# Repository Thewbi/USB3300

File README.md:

# USB3300
STM32F405RGT6 + USB3300

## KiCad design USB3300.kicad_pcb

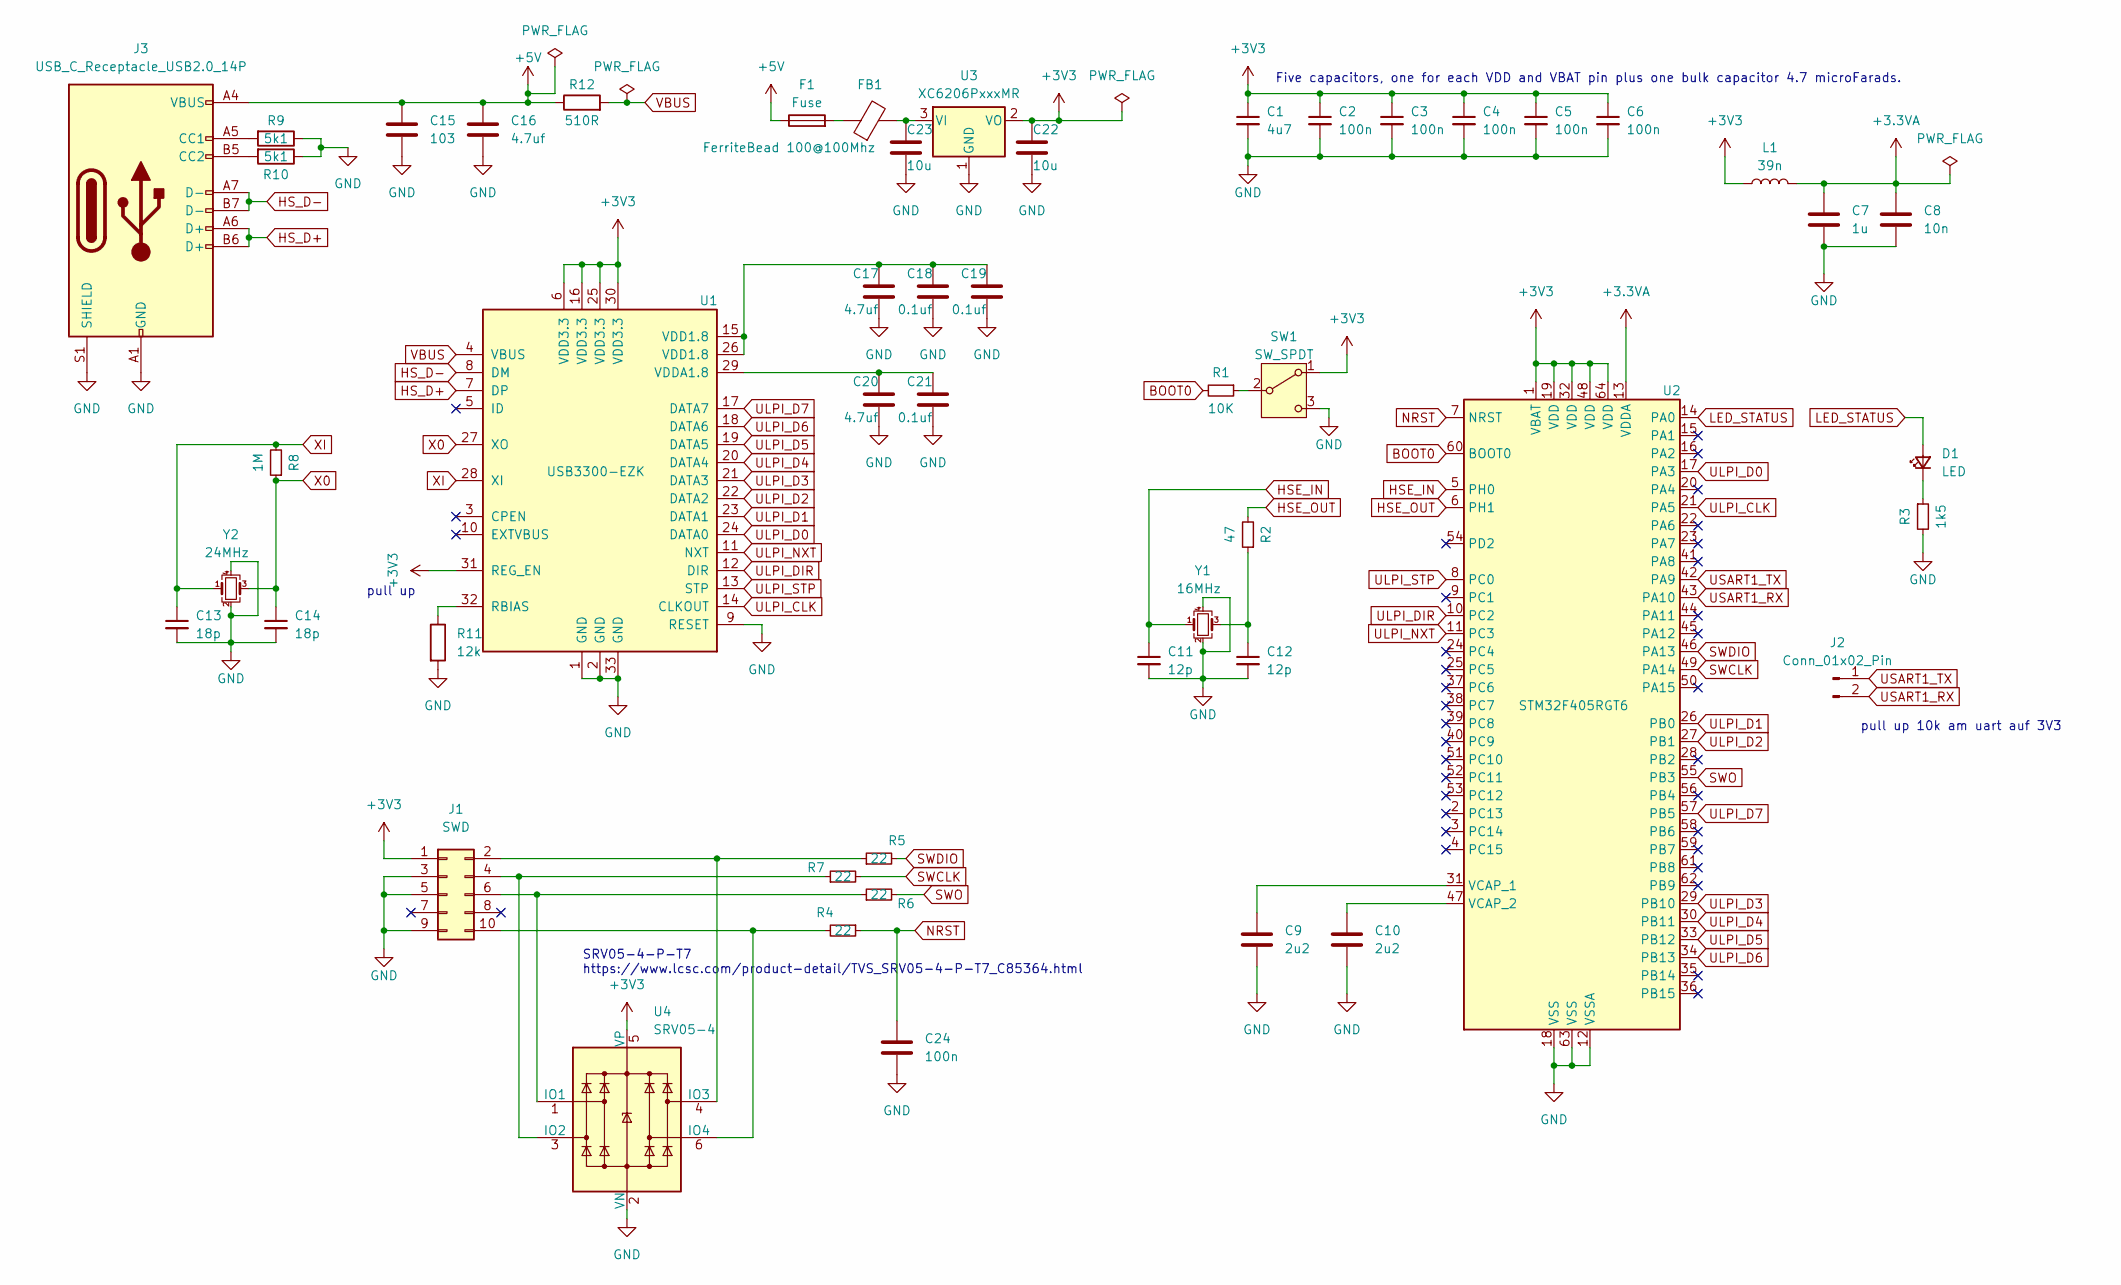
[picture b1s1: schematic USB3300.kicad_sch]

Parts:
C1: 4u7; C_0603_1608Metric
C2, C3, C4, C5, C6: 100n; C_0603_1608Metric
C7: 1u; C_0603_1608Metric
C8: 10n; C_0603_1608Metric
C9, C10: 2u2; C_0603_1608Metric
C11, C12: 12p; C_0402_1005Metric
C13, C14: 18p; C_0603_1608Metric
C15: 103; C_0603_1608Metric
C16, C17, C20: 4.7uf; C_0603_1608Metric
C18, C19, C21: 0.1uf; C_0603_1608Metric
C22, C23: 10u; C_0603_1608Metric
C24: 100n
D1: LED; LED_0402_1005Metric
F1: Fuse; Fuse_1206_3216Metric_Pad1.42x1.75mm_HandSolder
FB1: FerriteBead 100@100Mhz; LairdTech_28C0236-0JW-10
J1: SWD; PinHeader_2x05_P1.27mm_Vertical_SMD
J2: Conn_01x02_Pin; PinHeader_1x02_P2.54mm_Vertical
J3: USB_C_Receptacle_USB2.0_14P; USB_C_Receptacle_HRO_TYPE-C-31-M-12
L1: 39n; L_0603_1608Metric
R1: 10K; R_0603_1608Metric
R2: 47; R_0603_1608Metric
R3: 1k5; R_0603_1608Metric
R4, R5, R6, R7: 22; R_0603_1608Metric
R8: 1M; R_0603_1608Metric
R9, R10: 5k1; R_0603_1608Metric
R11: 12k; R_0603_1608Metric
R12: 510R; R_0603_1608Metric
SW1: SW_SPDT; SW_SPDT_PCM12
U1: USB3300-EZK; QFN-32-1EP_5x5mm_P0.5mm_EP3.45x3.45mm
U2: STM32F405RGT6; LQFP-64_10x10mm_P0.5mm
U3: XC6206PxxxMR; SOT-23-3
U4: SRV05-4; SOT-23-6
Y1: 16MHz; Crystal_SMD_3225-4Pin_3.2x2.5mm
Y2: 24MHz; Crystal_SMD_3225-4Pin_3.2x2.5mm

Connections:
+3.3VA: C7.1, C8.1, L1.2, U2.13 (VDDA)
+3V3: C1.1, C2.1, C3.1, C4.1, C5.1, C6.1, C22.1, J1.1, L1.1, SW1.1 (A), U1.6 (VDD3.3), U1.16 (VDD3.3), U1.25 (VDD3.3), U1.30 (VDD3.3), U1.31 (REG_EN), U2.1 (VBAT), U2.19 (VDD), U2.32 (VDD), U2.48 (VDD), U2.64 (VDD), U3.2 (VO), U4.5 (VP)
+5V: C15.1, C16.1, F1.1, J3.A4 (VBUS), J3.A9 (VBUS), J3.B4 (VBUS), J3.B9 (VBUS), R12.1
BOOT0: R1.2, U2.60 (BOOT0)
GND: C1.2, C2.2, C3.2, C4.2, C5.2, C6.2, C7.2, C8.2, C9.2, C10.2, C11.2, C12.2, C13.2, C14.2, C15.2, C16.2, C17.2, C18.2, C19.2, C20.2, C21.2, C22.2, C23.2, C24.2, J1.3, J1.5, J1.9, J3.A1 (GND), J3.A12 (GND), J3.B1 (GND), J3.B12 (GND), J3.S1 (SHIELD), R3.2, R9.1, R10.1, R11.2, SW1.3 (C), U1.1 (GND), U1.2 (GND), U1.9 (RESET), U1.33 (GND), U2.12 (VSSA), U2.18 (VSS), U2.63 (VSS), U3.1 (GND), U4.2 (VN), Y1.2, Y1.4, Y2.2, Y2.4
HSE_IN: C11.1, U2.5 (PH0), Y1.1
HSE_OUT: R2.2, U2.6 (PH1)
HS_D+: J3.A6 (D+), J3.B6 (D+), U1.7 (DP)
HS_D-: J3.A7 (D-), J3.B7 (D-), U1.8 (DM)
LED_STATUS: D1.2 (A), U2.14 (PA0)
NRST: C24.1, R4.1, U2.7 (NRST)
unnamed: C12.1, R2.1, Y1.3
unnamed: C17.1, C18.1, C19.1, U1.15 (VDD1.8), U1.26 (VDD1.8)
unnamed: D1.1 (K), R3.1
unnamed: F1.2, FB1.1
unnamed: J1.2, R5.1, U4.4 (IO3)
unnamed: J1.4, R7.1, U4.3 (IO2)
unnamed: J1.6, R6.1, U4.1 (IO1)
unnamed: J1.10, R4.2, U4.6 (IO4)
unnamed: J3.A5 (CC1), R9.2
unnamed: J3.B5 (CC2), R10.2
unnamed: R1.1, SW1.2 (B)
unnamed: R11.1, U1.32 (RBIAS)
unnamed: C20.1, C21.1, U1.29 (VDDA1.8)
unnamed: C9.1, U2.31 (VCAP_1)
unnamed: C10.1, U2.47 (VCAP_2)
unnamed: C23.1, FB1.2, U3.3 (VI)
SWCLK: R7.2, U2.49 (PA14)
SWDIO: R5.2, U2.46 (PA13)
SWO: R6.2, U2.55 (PB3)
ULPI_CLK: U1.14 (CLKOUT), U2.21 (PA5)
ULPI_D0: U1.24 (DATA0), U2.17 (PA3)
ULPI_D1: U1.23 (DATA1), U2.26 (PB0)
ULPI_D2: U1.22 (DATA2), U2.27 (PB1)
ULPI_D3: U1.21 (DATA3), U2.29 (PB10)
ULPI_D4: U1.20 (DATA4), U2.30 (PB11)
ULPI_D5: U1.19 (DATA5), U2.33 (PB12)
ULPI_D6: U1.18 (DATA6), U2.34 (PB13)
ULPI_D7: U1.17 (DATA7), U2.57 (PB5)
ULPI_DIR: U1.12 (DIR), U2.10 (PC2)
ULPI_NXT: U1.11 (NXT), U2.11 (PC3)
ULPI_STP: U1.13 (STP), U2.8 (PC0)
USART1_RX: J2.2, U2.43 (PA10)
USART1_TX: J2.1, U2.42 (PA9)
VBUS: R12.2, U1.4 (VBUS)
X0: C14.1, R8.1, U1.27 (XO), Y2.3
XI: C13.1, R8.2, U1.28 (XI), Y2.1

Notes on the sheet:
pull up
Five capacitors, one for each VDD and VBAT pin plus one bulk capacitor 4.7 microFarads.
pull up 10k am uart auf 3V3
SRV05-4-P-T7 https://www.lcsc.com/product-detail/TVS_SRV05-4-P-T7_C85364.html

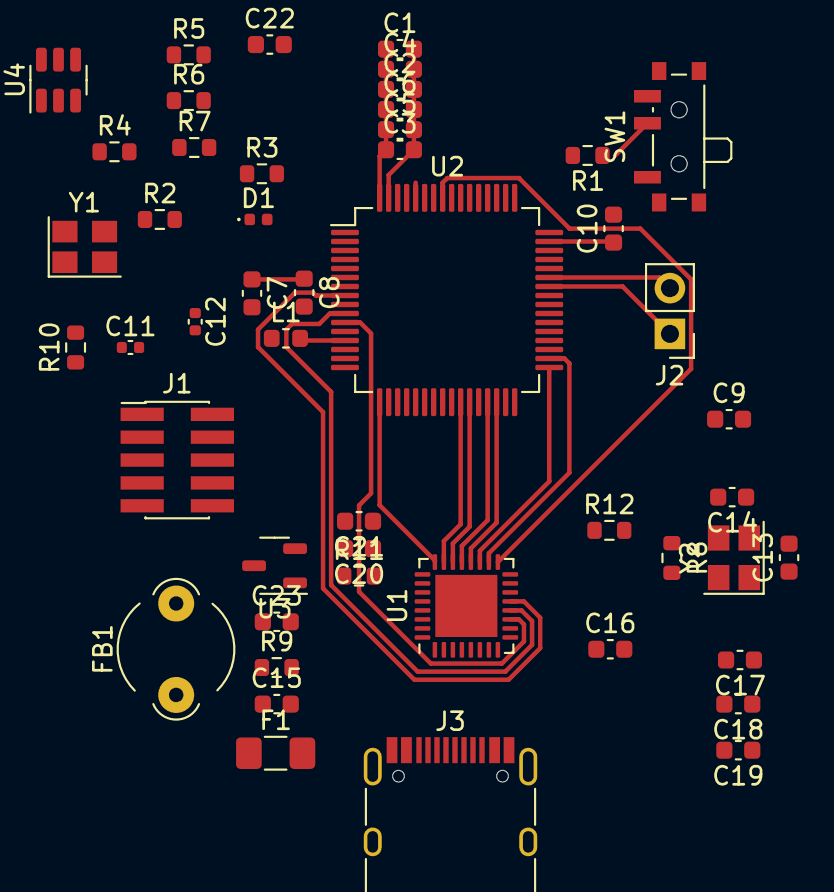
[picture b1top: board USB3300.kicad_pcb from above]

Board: 2 copper layers, 49 parts (0 on the bottom side), 47 nets.

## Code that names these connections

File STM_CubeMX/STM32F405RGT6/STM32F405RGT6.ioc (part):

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Mcu.Name=STM32F405RGTx
Mcu.Package=LQFP64
Mcu.UserName=STM32F405RGTx
PA10.Mode=Asynchronous
PA10.Signal=USART1_RX
PA3.Mode=OTG/Dual-Role-Device-HS
PA3.Signal=USB_OTG_HS_ULPI_D0
PA5.Mode=OTG/Dual-Role-Device-HS
PA5.Signal=USB_OTG_HS_ULPI_CK
PA9.Mode=Asynchronous
PA9.Signal=USART1_TX
PB0.Mode=OTG/Dual-Role-Device-HS
PB0.Signal=USB_OTG_HS_ULPI_D1
PB1.Mode=OTG/Dual-Role-Device-HS
PB1.Signal=USB_OTG_HS_ULPI_D2
PB10.Mode=OTG/Dual-Role-Device-HS
PB10.Signal=USB_OTG_HS_ULPI_D3
PB11.Mode=OTG/Dual-Role-Device-HS
PB11.Signal=USB_OTG_HS_ULPI_D4
PB12.Mode=OTG/Dual-Role-Device-HS
PB12.Signal=USB_OTG_HS_ULPI_D5
PB13.Mode=OTG/Dual-Role-Device-HS
PB13.Signal=USB_OTG_HS_ULPI_D6
PB5.Mode=OTG/Dual-Role-Device-HS
PB5.Signal=USB_OTG_HS_ULPI_D7
PC0.Mode=OTG/Dual-Role-Device-HS
PC0.Signal=USB_OTG_HS_ULPI_STP
PC2.Mode=OTG/Dual-Role-Device-HS
PC2.Signal=USB_OTG_HS_ULPI_DIR
PC3.Mode=OTG/Dual-Role-Device-HS
PC3.Signal=USB_OTG_HS_ULPI_NXT
RCC.HSE_VALUE=25000000
RCC.SYSCLKFreq_VALUE=16000000
board=custom

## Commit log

2024-02-01 Adding the CubeMX projects for documenting the pinout and firmware source code.
2024-02-05 Added power_flags to lower the amount of warnings, fixed +3V3 label
2024-02-05 layout
2024-02-14 work on pcb
